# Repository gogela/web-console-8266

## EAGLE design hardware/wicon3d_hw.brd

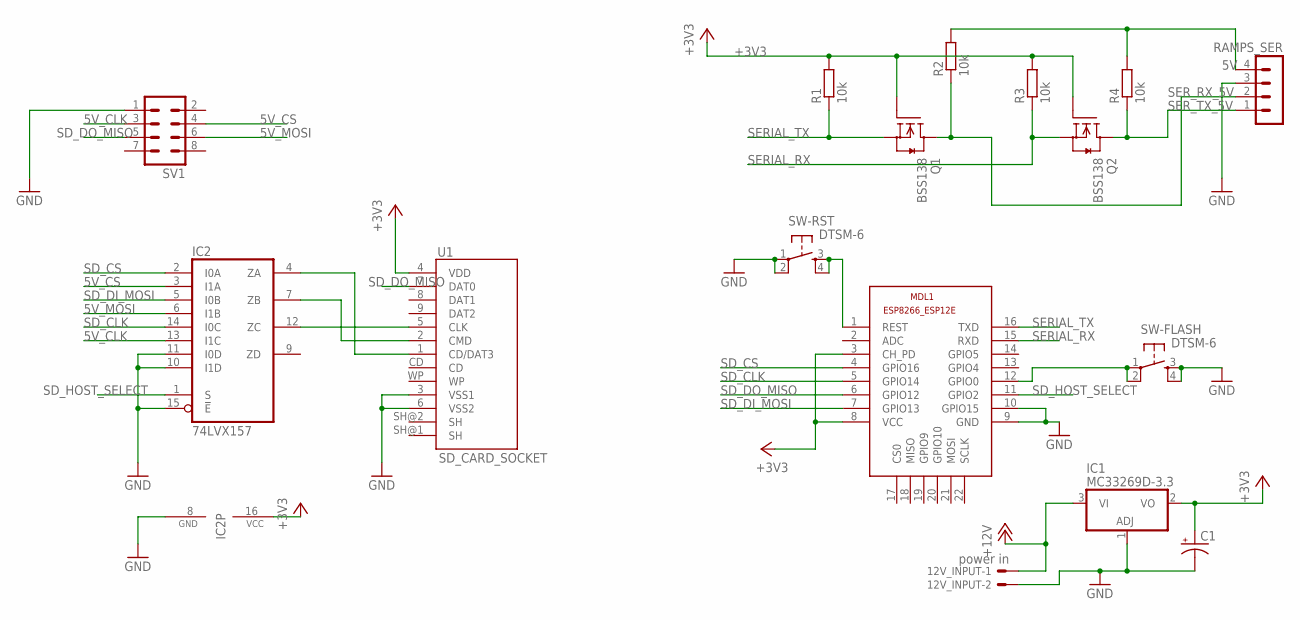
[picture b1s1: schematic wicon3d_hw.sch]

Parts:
12V_INPUT: power in; 22-23-2021
C1: 47UF-50V-20%(ELECT); PANASONIC_D
IC1: MC33269D-3.3; DPACK
IC2: 74LVX157; TSSOP16L
MDL1: ESP8266-12EESP8266-ESP12E; ESP8266-ESP12E
Q1, Q2: BSS138; SOT23
R1, R2, R3, R4: 10k; R0805
RAMPS_SER: MA04-1
SV1: MA04-2
SW-FLASH: DTSM-6
SW-RST: DTSM-6
U1: SD_CARD_SOCKET; SD_1:1

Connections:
5V: R2.2, R4.2, RAMPS_SER.4
5V_CLK: IC2.13 (I1C), SV1.3
5V_CS: IC2.3 (I1A), SV1.4
5V_MOSI: IC2.6 (I1B), SV1.6
+3V3: C1.+, IC1.2 (VO), IC2.16 (VCC), MDL1.3 (CH_PD), MDL1.8 (VCC), Q1.1 (G), Q2.1 (G), R1.2, R3.2, U1.4 (VDD)
+12V: 12V_INPUT.1, IC1.3 (VI)
CLK: IC2.12 (ZC), U1.5 (CLK)
CS: IC2.4 (ZA), U1.1 (CD/DAT3)
GND: 12V_INPUT.2, C1.-, IC1.1 (ADJ), IC2.8 (GND), IC2.10 (I1D), IC2.11 (I0D), IC2.15 (!E), MDL1.9 (GND), MDL1.10 (GPIO15), RAMPS_SER.3, SV1.1, SW-FLASH.3, SW-FLASH.4, SW-RST.1, SW-RST.2, U1.3 (VSS1), U1.6 (VSS2)
MOSI: IC2.7 (ZB), U1.2 (CMD)
unnamed: MDL1.1 (REST), SW-RST.3, SW-RST.4
unnamed: MDL1.12 (GPIO0), SW-FLASH.1, SW-FLASH.2
unnamed: MDL1.20 (GPIO10), MDL1.21 (MOSI), MDL1.22 (SCLK)
SD_CLK: IC2.14 (I0C), MDL1.5 (GPIO14)
SD_CS: IC2.2 (I0A), MDL1.4 (GPIO16)
SD_DI_MOSI: IC2.5 (I0B), MDL1.7 (GPIO13)
SD_DO_MISO: MDL1.6 (GPIO12), SV1.5, U1.7 (DAT0)
SD_HOST_SELECT: IC2.1 (S), MDL1.11 (GPIO2)
SERIAL_RX: MDL1.15 (RXD), Q2.2 (S), R3.1
SERIAL_TX: MDL1.16 (TXD), Q1.2 (S), R1.1
SER_RX_5V: Q1.3 (D), R2.1, RAMPS_SER.2
SER_TX_5V: Q2.3 (D), R4.1, RAMPS_SER.1

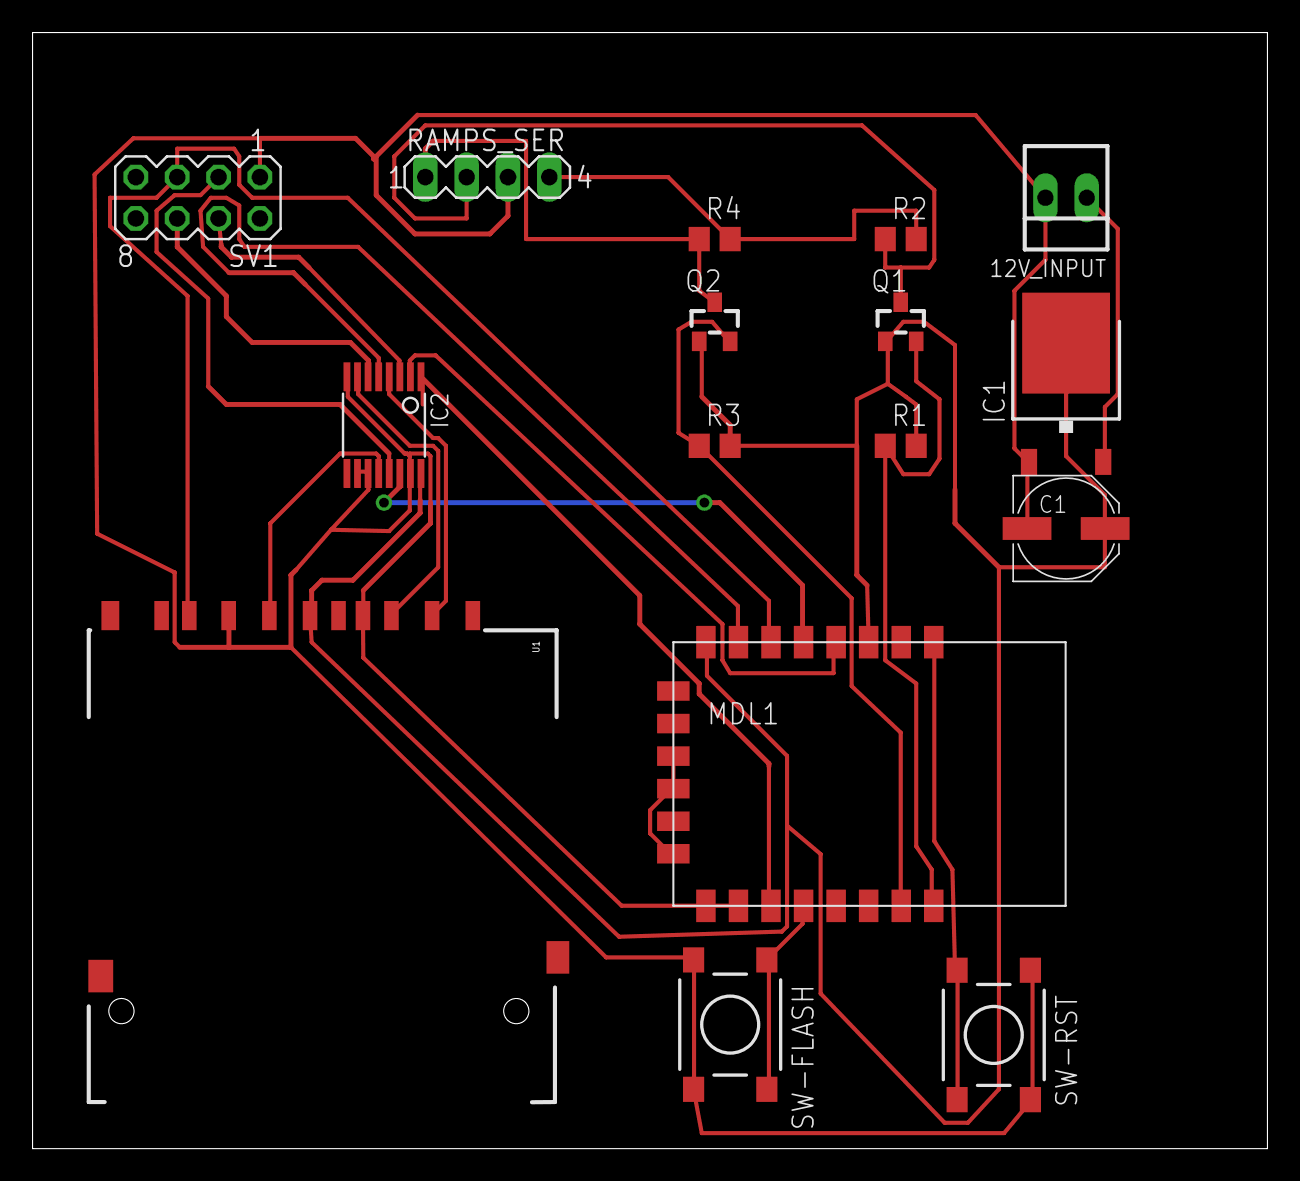
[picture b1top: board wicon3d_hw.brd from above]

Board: 2 copper layers, 75.9 x 68.6 mm, 16 parts (0 on the bottom side), 22 nets.

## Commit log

2016-09-26 1st working version

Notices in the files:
parts and their libraries:
SparkFun-Capacitors: Licensing: Creative Commons ShareAlike 4.0 International - https://creativecommons.org/licenses/by-sa/4.0
m-pad-2.1: License : GNU General Public License version 2 (see bottom)
